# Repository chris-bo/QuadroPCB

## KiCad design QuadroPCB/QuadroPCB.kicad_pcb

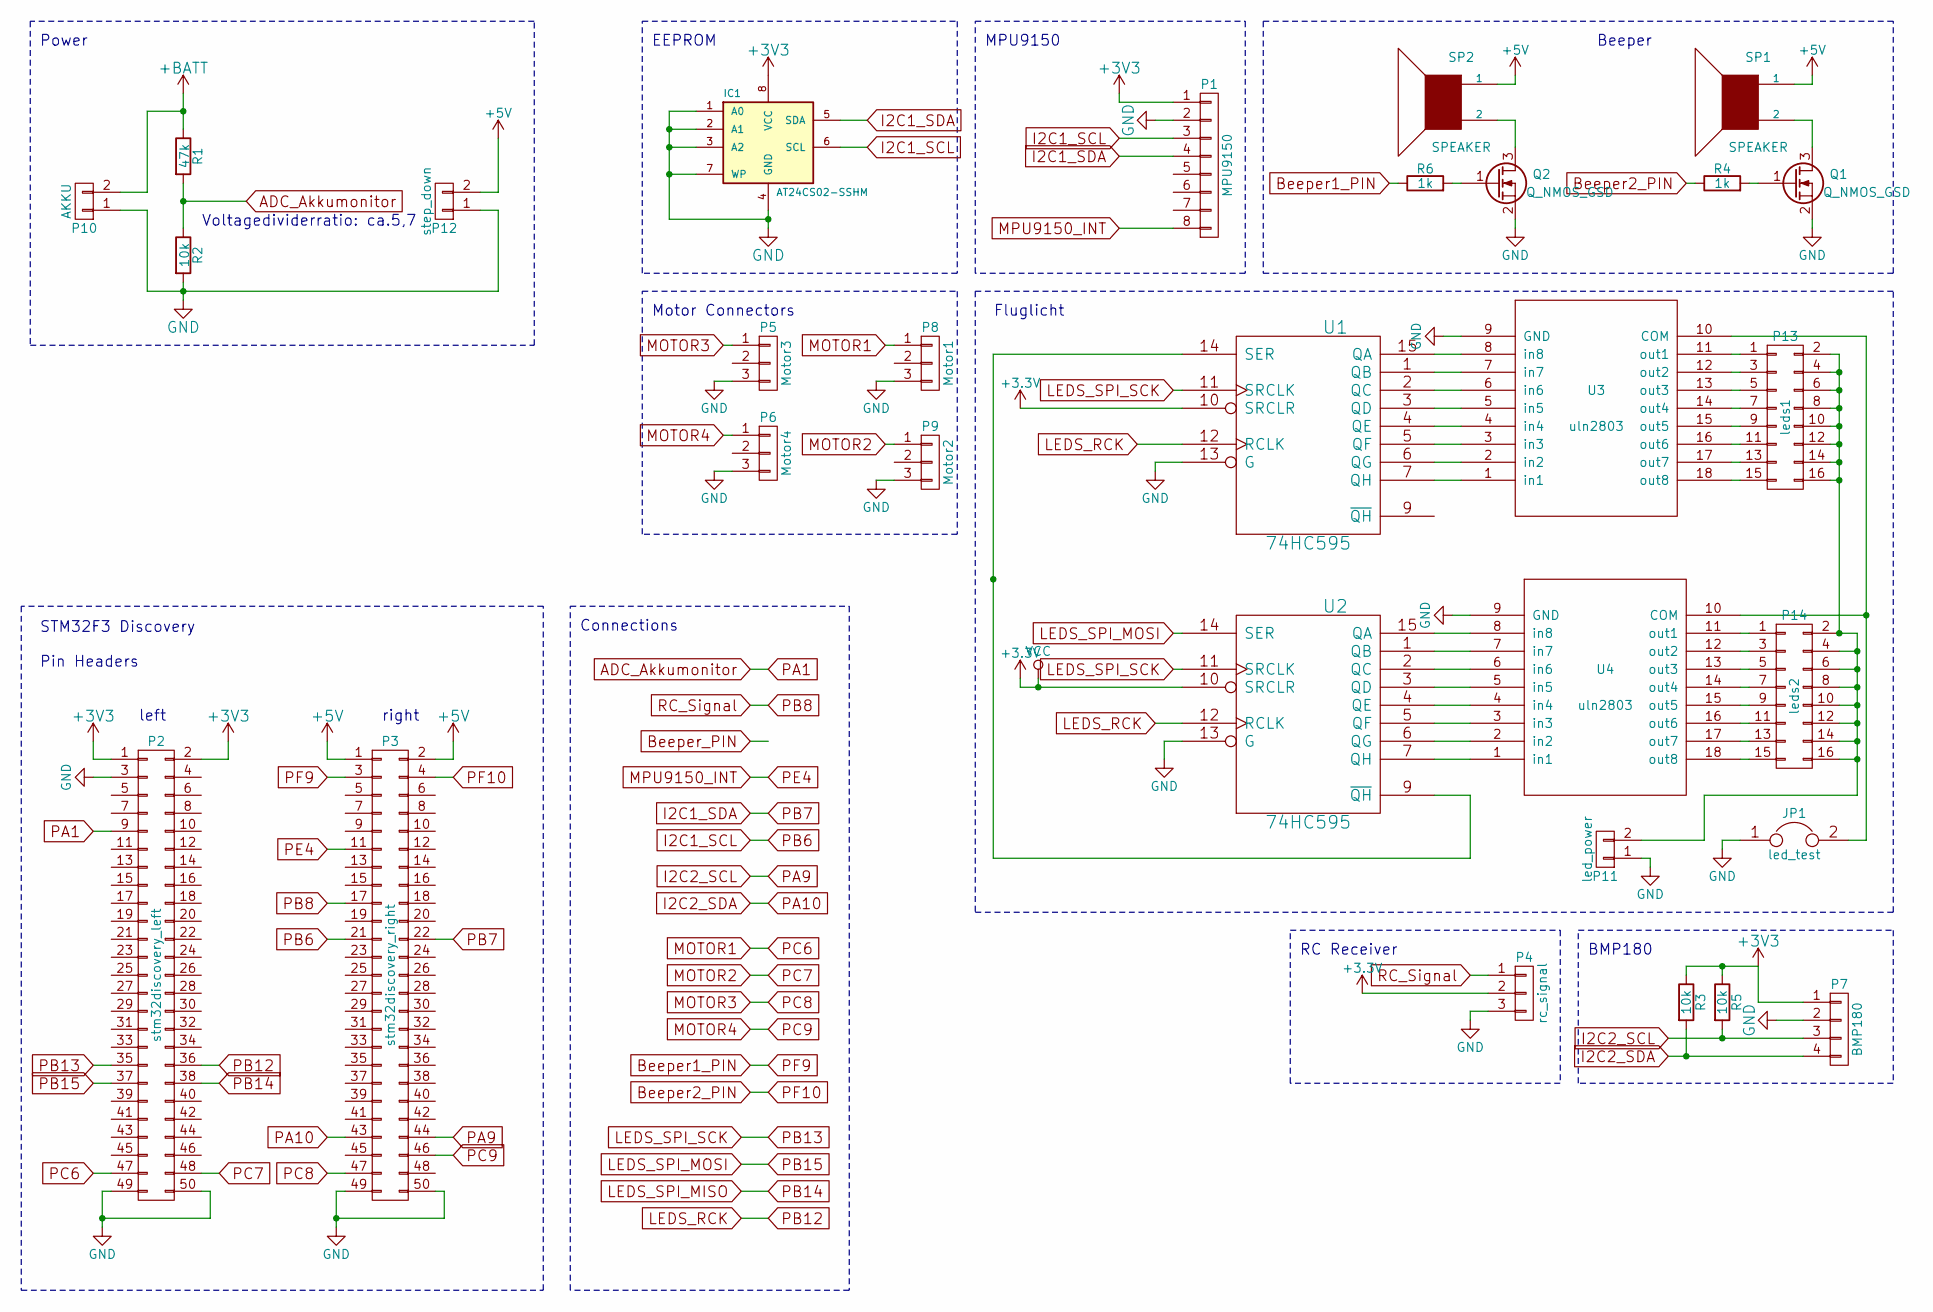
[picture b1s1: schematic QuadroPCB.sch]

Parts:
IC1: AT24CS02-SSHM; DIP-8__300_ELL
JP1: led_test; Pin_Header_Straight_1x02
P1: MPU9150; Pin_Header_Straight_1x08
P2: stm32discovery_left; Pin_Header_Straight_2x25
P3: stm32discovery_right; Pin_Header_Straight_2x25
P4: rc_signal; Pin_Header_Straight_1x03
P5: Motor3; Pin_Header_Straight_1x03
P6: Motor4; Pin_Header_Straight_1x03
P7: BMP180; Pin_Header_Straight_1x04
P8: Motor1; Pin_Header_Straight_1x03
P9: Motor2; Pin_Header_Straight_1x03
P10: AKKU; PINHEAD1-2
P11: led_power; PINHEAD1-2
P12: step_down; PINHEAD1-2
P13: leds1; Pin_Header_Straight_2x08
P14: leds2; Pin_Header_Straight_2x08
Q1, Q2: Q_NMOS_GSD; SOT-23_Handsoldering
R1: 47k; R_0805_HandSoldering
R2, R3, R5: 10k; R_0805_HandSoldering
R4, R6: 1k; R_0805_HandSoldering
SP1, SP2: SPEAKER; Buzzer_12x9.5RM7.6
U1, U2: 74HC595; SOIC-16_3.9x9.9mm_Pitch1.27mm
U3, U4: uln2803; SOIC-18_7.5x11.6mm_Pitch1.27mm

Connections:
+5V: P3.1, P3.2, P12.2, SP1.1, SP2.1
+BATT: P10.2, R1.1
ADC_Akkumonitor: P2.9, R1.2, R2.1
Beeper1_PIN: P3.3, R6.1
GND: IC1.1 (A0), IC1.2 (A1), IC1.3 (A2), IC1.4 (GND), IC1.7 (WP), JP1.1, P1.2, P2.3, P2.49, P2.50, P3.49, P3.50, P4.3, P5.3, P6.3, P7.2, P8.3, P9.3, P10.1, P11.1, P12.1, Q1.2 (S), Q2.2 (S), R2.2, U1.8 (GND), U1.13 (G), U2.8 (GND), U2.13 (G), U3.9 (GND), U4.9 (GND)
I2C1_SCL: IC1.6 (SCL), P1.3, P3.21
I2C1_SDA: IC1.5 (SDA), P1.4, P3.22
LEDS_RCK: P2.36, U1.12 (RCLK), U2.12 (RCLK)
LEDS_SPI_MOSI: P2.37, U2.14 (SER)
LEDS_SPI_SCK: P2.35, U1.11 (SRCLK), U2.11 (SRCLK)
MOTOR1: P2.47, P8.1
MOTOR3: P3.47, P5.1
MOTOR4: P3.46, P6.1
unnamed: JP1.2, U3.10 (COM), U4.10 (COM)
unnamed: P11.2, P13.2, P13.4, P13.6, P13.8, P13.10, P13.12, P13.14, P13.16, P14.2, P14.4, P14.6, P14.8, P14.10, P14.12, P14.14, P14.16
unnamed: P13.1, U3.11 (out1)
unnamed: P13.3, U3.12 (out2)
unnamed: P13.5, U3.13 (out3)
unnamed: P13.7, U3.14 (out4)
unnamed: P13.9, U3.15 (out5)
unnamed: P13.11, U3.16 (out6)
unnamed: P13.13, U3.17 (out7)
unnamed: P13.15, U3.18 (out8)
unnamed: P14.1, U4.11 (out1)
unnamed: P14.3, U4.12 (out2)
unnamed: P14.5, U4.13 (out3)
unnamed: P14.7, U4.14 (out4)
unnamed: P14.9, U4.15 (out5)
unnamed: P14.11, U4.16 (out6)
unnamed: P14.13, U4.17 (out7)
unnamed: P14.15, U4.18 (out8)
unnamed: Q1.1 (G), R4.2
unnamed: Q1.3 (D), SP1.2
unnamed: Q2.1 (G), R6.2
unnamed: Q2.3 (D), SP2.2
unnamed: U1.1 (QB), U3.7 (in7)
unnamed: U1.2 (QC), U3.6 (in6)
unnamed: U1.3 (QD), U3.5 (in5)
unnamed: U1.4 (QE), U3.4 (in4)
unnamed: U1.5 (QF), U3.3 (in3)
unnamed: U1.6 (QG), U3.2 (in2)
unnamed: U1.7 (QH), U3.1 (in1)
unnamed: U1.14 (SER), U2.9 (~QH)
unnamed: U1.15 (QA), U3.8 (in8)
unnamed: U2.1 (QB), U4.7 (in7)
unnamed: U2.2 (QC), U4.6 (in6)
unnamed: U2.3 (QD), U4.5 (in5)
unnamed: U2.4 (QE), U4.4 (in4)
unnamed: U2.5 (QF), U4.3 (in3)
unnamed: U2.6 (QG), U4.2 (in2)
unnamed: U2.7 (QH), U4.1 (in1)
unnamed: U2.15 (QA), U4.8 (in8)
PA9: P3.44, P7.3, R5.2
PA10: P3.43, P7.4, R3.2
PB8: P3.17, P4.1
PB14: P2.38
PC7: P2.48, P9.1
PE4: P1.8, P3.11
PF10: P3.4, R4.1

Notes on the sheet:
Voltagedividerratio: ca.5,7
MPU9150
Beeper
BMP180
EEPROM
STM32F3 Discovery Pin Headers
left
right
RC Receiver
Motor Connectors
Power
Connections
Fluglicht

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
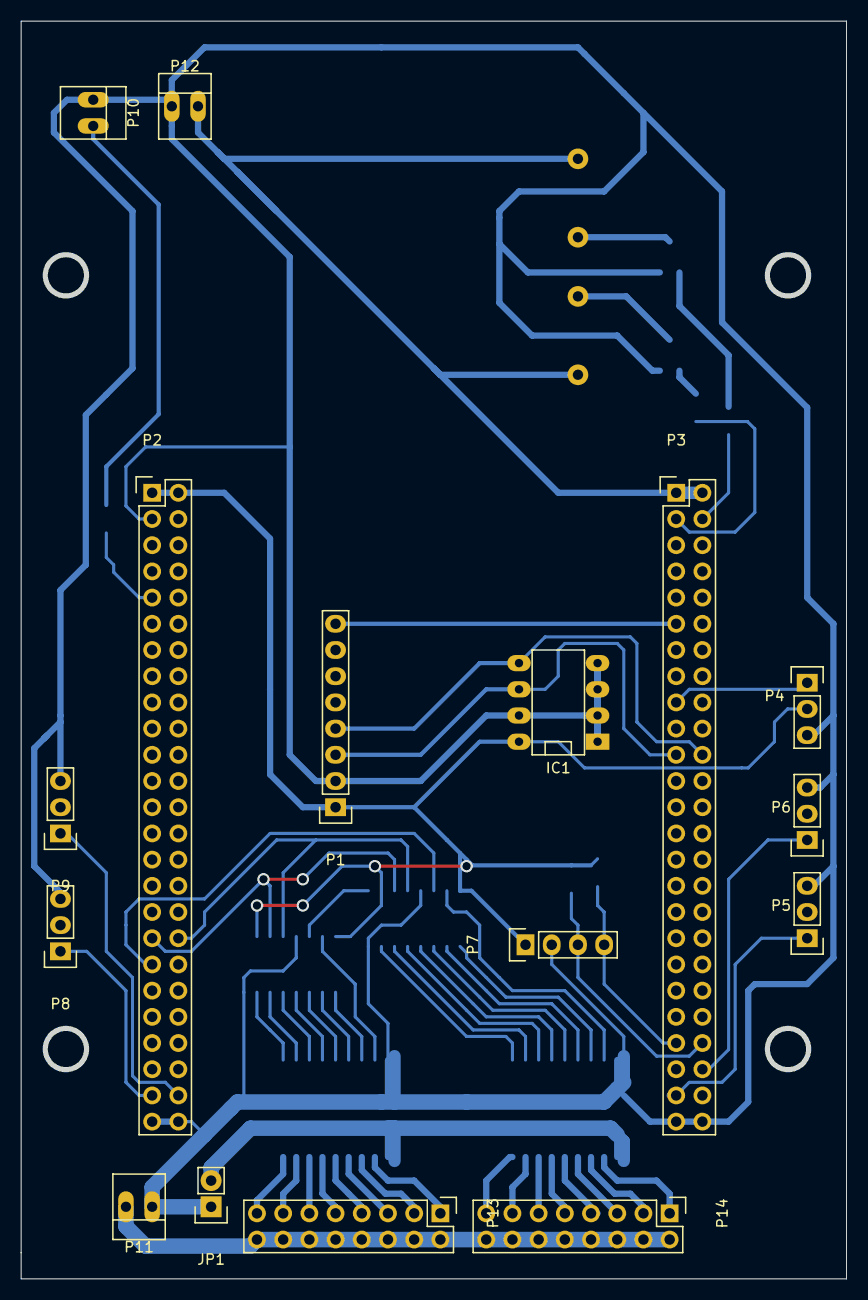
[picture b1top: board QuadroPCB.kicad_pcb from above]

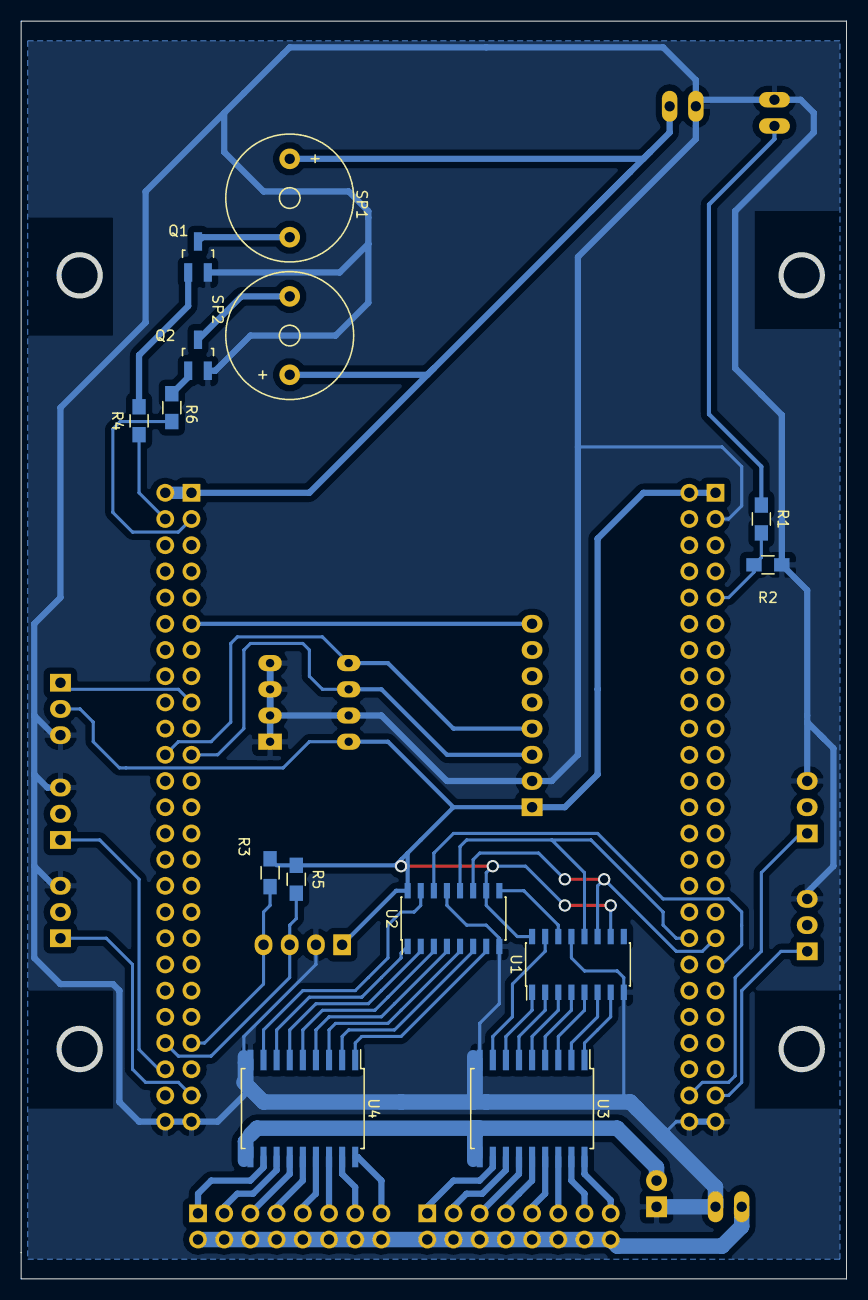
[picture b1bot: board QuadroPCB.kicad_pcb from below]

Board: 2 copper layers, 79.6 x 121.5 mm, 30 parts (14 on the bottom side), 59 nets.

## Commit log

2015-04-27 first commit added todo
2015-04-27 spannungsversorgung
2015-04-28 kicad projekt erstellt
2015-04-30 added datasheets add step-down converter
2015-04-30 Updated schematic rc receiver, bmp180, motor, eeprom added more datasheets
2015-04-30 added datasheets eeprom + bss123 nmos transistor
2015-04-30 updated connections
2015-05-02 blub
2015-05-02 dei mudder commitet
2015-05-04 neuer step down
2015-05-13 blubb
2015-05-25 step down extern fluglicht auf die platine gepackt
2015-06-03 version 1
